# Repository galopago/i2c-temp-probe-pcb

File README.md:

# PROBE STYLE I2C TEMPERATURE SENSOR PCB

Small circuit board, designed to be installed inside a metal tube or thermowell.

Read this in other languages: [Español](/assets/markdown/README.es.md)

Imagine this scenario: you have a bunch of I2C sensors tied to a bus (i.e. Humidity, pressure, light) and a waterproof temperature sensor is needed, the fastest option is to acquire one of the very popular OneWire type. This brings two big disadvantages:

* An additional GPIO pin (and wire!) is required, because I2C signals are incompatible with OneWire
* Additional libraries will be needed, protocols are very dissimilar in software too

There are very few waterproof temperature sensors in the market with a real I2C interface, but are not easy to obtain and are expensive. This document gives you some ideas on how to build your own waterproof I2C temperature sensor in an affordable way.

## Main features
* Open source
* Designed in KiCad PCB
* All source files available
* Gerber files available : single piece or 100x100mm panel
* Assorted flavors

## Printed circuit board

The PCB was designed to be as small as possible, but using SMD components that can be hand soldered. All pull-up resistors can be populated on the board. There are also onboard solder jumper pads for I2C address setup.

## Wiring

Multi conductor cable with 5 stranded wires used for VCC,GND,SDA,SCL and ALARM signals

## Waterproofing

The board could be fitted inside a stainless steel tube or thermowell. Some thermal silicone grease must be applied in the sensor zone, and epoxy glue near the cable input for sealing 

## Versions

There are several board versions, each one with different sensor and PCB sizes

| SENSOR  | SIZE        | LINK                                   |
|---------|-------------|----------------------------------------|
| LM75A   |  5.5x35mm   | [lm75A-probe-pcb](/lm75A-probe-pcb)    |
| PCT2075 |  4.0x35mm   | [pct2075-probe-pcb](/pct2075-probe-pcb)|

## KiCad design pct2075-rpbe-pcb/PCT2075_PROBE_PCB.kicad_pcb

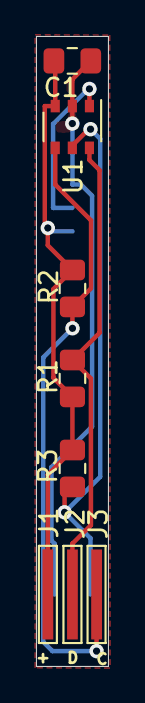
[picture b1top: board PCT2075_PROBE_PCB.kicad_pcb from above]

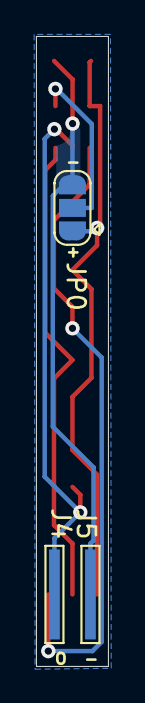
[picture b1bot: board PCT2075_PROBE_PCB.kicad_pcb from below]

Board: 2 copper layers, 4.0 x 35.0 mm, 11 parts (3 on the bottom side), 6 nets.

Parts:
C1: C; C_0805_2012Metric_Pad1.15x1.40mm_HandSolder
J1, J2, J3, J4, J5: Conn_01x01_Female; StrandedWire_Pad_0.6x5.0mm
JP0: SolderJumper_3_Open; SolderJumper-3_P1.3mm_Open_RoundedPad1.0x1.5mm
R1, R2, R3: R; R_0805_2012Metric_Pad1.15x1.40mm_HandSolder
U1: PCT2075GV; TSOP-6_1.65x3.05mm_P0.95mm

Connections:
unnamed: C1.1, J1.1, JP0.1, R1.1, R2.1, R3.1, U1.3
unnamed: C1.2, J5.1, JP0.3, U1.2
unnamed: J2.1, R1.2, U1.6
unnamed: J3.1, R2.2, U1.4
unnamed: J4.1, R3.2, U1.5
unnamed: JP0.2, U1.1

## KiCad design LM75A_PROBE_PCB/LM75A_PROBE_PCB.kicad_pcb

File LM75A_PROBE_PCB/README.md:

# PROBE STYLE I2C TEMPERATURE SENSOR PCB

Small circuit board(5.5x35mm), based on [LM75A](assets/pdf/lm75a.pdf) chip, designed to be installed inside a metal tube or thermowell.

## How to use this repository

The PCB was developed in KiCad V5.1,

## Directory structure

* The root folder contains template KiCad files: project, schematic and PCB 
* /modules folder contains additional footprints needed to edit printed circuit board
* /gerber folder contains ready to manufacture files.
* /assets folder contains support files for reade.md

## Board pinout

## Panelized boards

## Wired board

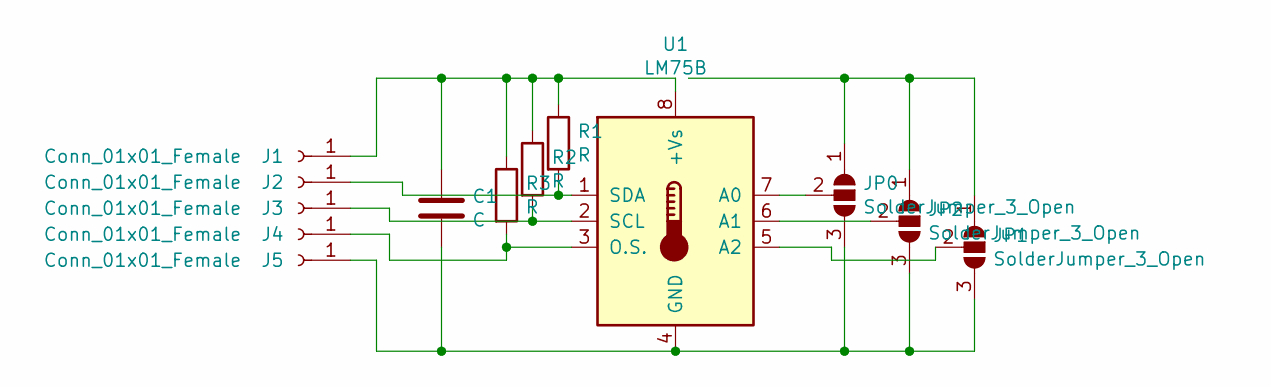
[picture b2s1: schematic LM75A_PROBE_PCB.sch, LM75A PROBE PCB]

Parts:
C1: C; C_0805_2012Metric_Pad1.15x1.40mm_HandSolder
J1, J2, J3, J4, J5: Conn_01x01_Female; StrandedWire_Pad_0.6x5.0mm
JP0, JP1, JP2: SolderJumper_3_Open; SolderJumper-3_P1.3mm_Open_RoundedPad1.0x1.5mm
R1, R2, R3: R; R_0805_2012Metric_Pad1.15x1.40mm_HandSolder
U1: LM75B; SOIC-8_3.9x4.9mm_P1.27mm

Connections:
unnamed: C1.1, J1.1, R1.1, R2.1, R3.1, U1.8 (+Vs)
unnamed: C1.2, J5.1, JP0.3 (B), JP1.3 (B), JP2.3 (B), U1.4 (GND)
unnamed: J2.1, R1.2, U1.1 (SDA)
unnamed: J3.1, R2.2, U1.2 (SCL)
unnamed: J4.1, R3.2, U1.3 (O.S.)
unnamed: JP0.1 (A), JP1.1 (A), JP2.1 (A)
unnamed: JP0.2 (C), U1.7 (A0)
unnamed: JP1.2 (C), U1.5 (A2)
unnamed: JP2.2 (C), U1.6 (A1)

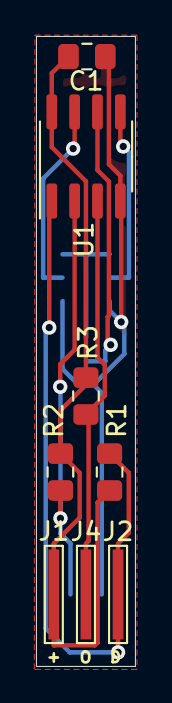
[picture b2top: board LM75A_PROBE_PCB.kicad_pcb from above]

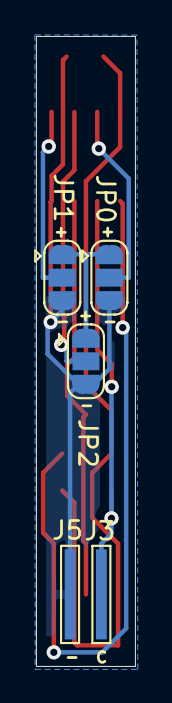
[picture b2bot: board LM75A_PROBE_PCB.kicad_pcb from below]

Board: 2 copper layers, 5.5 x 35.0 mm, 13 parts (5 on the bottom side), 9 nets.

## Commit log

2022-02-13 unified folders
2022-02-13 starter template
2022-02-13 starting spanish
2022-02-13 spanish doeing
2022-02-13 spanish doeing more
2022-02-13 spanish finishing
2022-02-13 spanish finished
2022-02-13 spanish finished and cheked
2022-02-13 english started
2022-02-13 english starting
2022-02-13 english starting+
2022-02-13 english starting++
2022-02-13 english finished
2022-02-14 images
2022-02-14 pinout
2022-02-14 pinout fixes
2022-02-15 LM75A readme started
2022-02-15 testing relative path
2022-02-15 pictures added
2022-02-15 pct2075 readme started
2022-02-15 temp probe finished
2022-02-15 typo
2022-03-01 doc:(I2C_TEMP_PROBE ROOT)thermowell add pic
2022-03-11 doc:(i2c-temp-probe-pcb ROOT)renamed repo,folder changed links
2022-03-11 doc:(i2c-temp-probe-pcb ROOT)renamed repo,folder changed links+
2022-03-15 doc:(i2c-temp-probe-pcb root)license
